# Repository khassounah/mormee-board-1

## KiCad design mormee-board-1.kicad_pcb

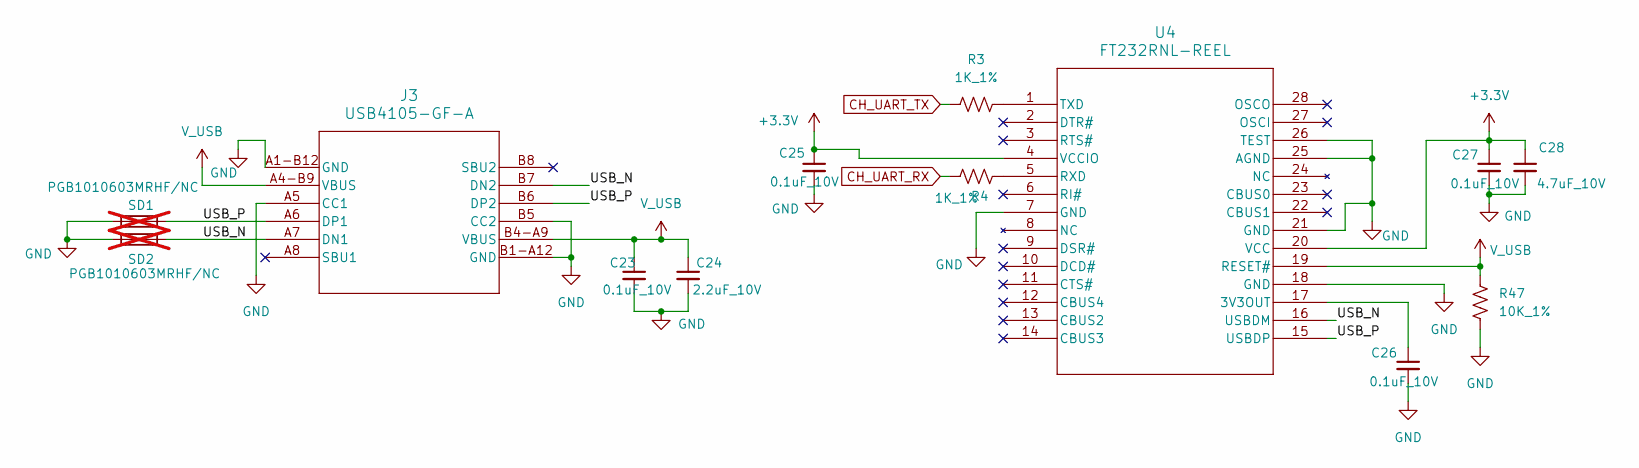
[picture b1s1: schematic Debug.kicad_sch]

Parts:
C23, C25, C26, C27: 0.1uF_10V; C_0603_1608Metric
C24: 2.2uF_10V; C_0603_1608Metric
C28: 4.7uF_10V; C_0603_1608Metric
J3: USB4105-GF-A; USB4105_GCT
R3, R4: 1K_1%; R_0603_1608Metric
R47: 10K_1%; R_0603_1608Metric
SD1, SD2: PGB1010603MRHF/NC; Fuse_0603_1608Metric; not fitted
U4: FT232RNL-REEL; SSOP-28_FTD

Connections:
+3.3V: C25.1, C27.1, C28.1, U4.4 (VCCIO), U4.20 (VCC); also elsewhere on the board
/Debug Interface/USB_N: J3.A7 (DN1), J3.B7 (DN2), SD2.2, U4.16 (USBDM)
/Debug Interface/USB_P: J3.A6 (DP1), J3.B6 (DP2), SD1.2, U4.15 (USBDP)
CH_UART_RX: R4.1; also elsewhere on the board
CH_UART_TX: R3.2; also elsewhere on the board
GND: C23.2, C24.2, C25.2, C26.2, C27.2, C28.2, J3.A1-B12 (GND), J3.A5 (CC1), J3.B1-A12 (GND), J3.B5 (CC2), R47.2, SD1.1, SD2.1, U4.7 (GND), U4.18 (GND), U4.21 (GND), U4.25 (AGND), U4.26 (TEST); also elsewhere on the board
unnamed: C26.1, U4.17 (3V3OUT)
unnamed: R4.2, U4.5 (RXD)
unnamed: R3.1, U4.1 (TXD)
V_USB: C23.1, C24.1, J3.A4-B9 (VBUS), J3.B4-A9 (VBUS), R47.1, U4.19 (RESET#); also elsewhere on the board

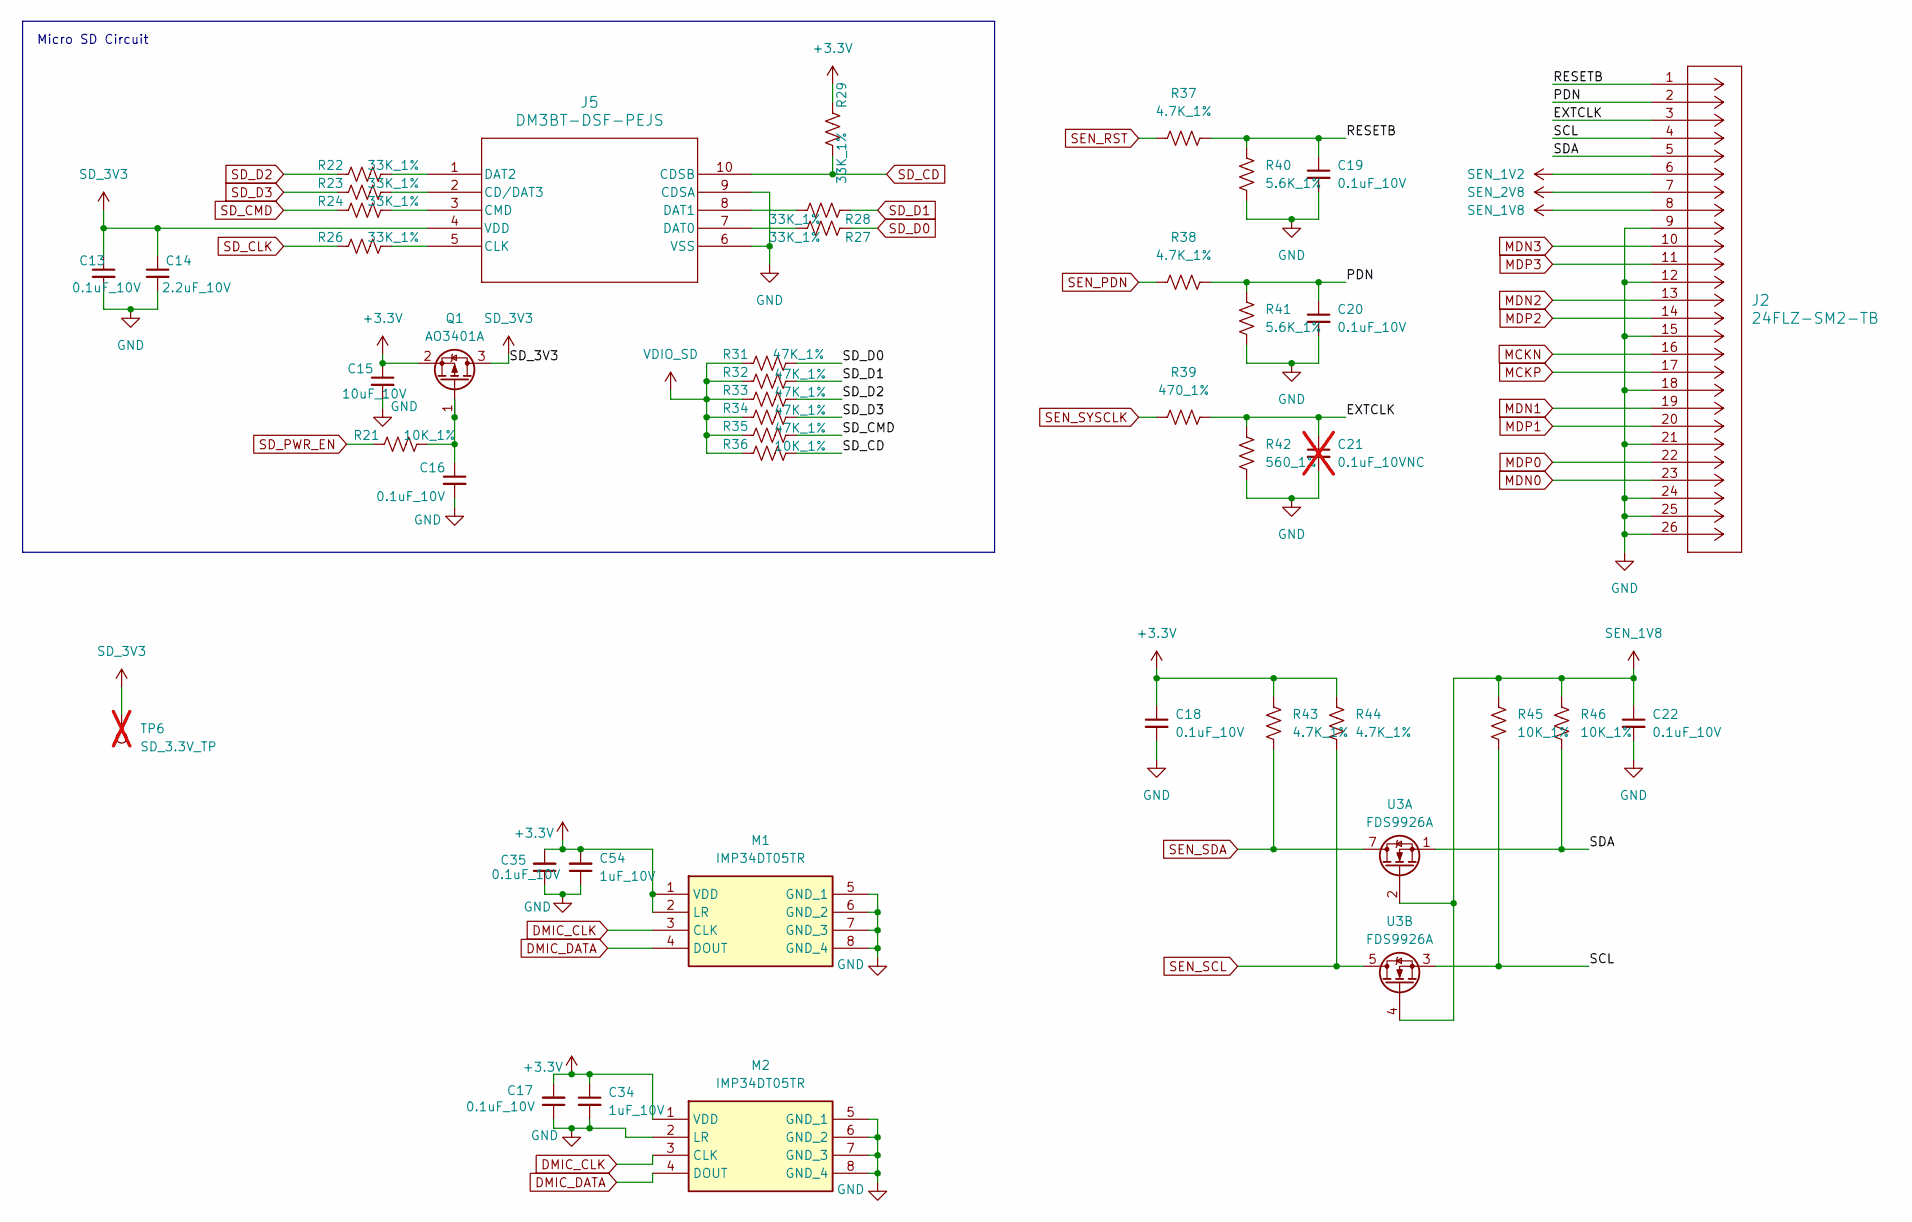
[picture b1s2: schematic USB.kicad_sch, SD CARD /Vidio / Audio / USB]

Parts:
C13, C16, C17, C18, C19, C20, C22, C35: 0.1uF_10V; C_0603_1608Metric
C14: 2.2uF_10V; C_0603_1608Metric
C15: 10uF_10V; C_0603_1608Metric
C21: 0.1uF_10VNC; C_0603_1608Metric; not fitted
C34, C54: 1uF_10V; C_0603_1608Metric
J2: 24FLZ-SM2-TB; CON24_1X24_DB_JST
J5: DM3BT-DSF-PEJS; DM3BT-DSF-PEJS_HIR
M1, M2: IMP34DT05TR; Manufacturer_Part_Number IMP34DT05TR; Mouser Part Number 511-IMP34DT05TR
Q1: AO3401A; SOT-23
R21, R36, R45, R46: 10K_1%; R_0603_1608Metric
R22, R23, R24, R26, R27, R28, R29: 33K_1%; R_0603_1608Metric
R31, R32, R33, R34, R35: 47K_1%; R_0603_1608Metric
R37, R38, R43, R44: 4.7K_1%; R_0603_1608Metric
R39: 470_1%; R_0603_1608Metric
R40, R41: 5.6K_1%; R_0603_1608Metric
R42: 560_1%; R_0603_1608Metric
TP6: SD_3.3V_TP; TestPoint_Pad_D1.5mm; not fitted
U3: FDS9926A; SOIC-8_3.9x4.9mm_P1.27mm

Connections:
+3.3V: C15.1, C17.2, C18.1, C34.1, C35.2, C54.2, M1.1 (VDD), M1.2 (LR), M2.1 (VDD), Q1.2 (S), R29.1, R43.1, R44.1; also elsewhere on the board
/SD CARD /Vidio / Audio / USB/EXTCLK: C21.1, J2.3, R39.1, R42.1
/SD CARD /Vidio / Audio / USB/PDN: C20.1, J2.2, R38.1, R41.1
/SD CARD /Vidio / Audio / USB/RESETB: C19.1, J2.1, R37.1, R40.1
/SD CARD /Vidio / Audio / USB/SCL: J2.4, R45.2, U3.3 (S2)
/SD CARD /Vidio / Audio / USB/SDA: J2.5, R46.2, U3.1 (S1)
DMIC_CLK: M1.3 (CLK), M2.3 (CLK); also elsewhere on the board
DMIC_DATA: M1.4 (DOUT), M2.4 (DOUT); also elsewhere on the board
GND: C13.2, C14.2, C15.2, C16.2, C17.1, C18.2, C19.2, C20.2, C21.2, C22.2, C34.2, C35.1, C54.1, J2.9, J2.12, J2.15, J2.18, J2.21, J2.24, J2.25, J2.26, J5.6 (VSS), J5.9 (CDSA), M1.5 (GND_1), M1.6 (GND_2), M1.7 (GND_3), M1.8 (GND_4), M2.2 (LR), M2.5 (GND_1), M2.6 (GND_2), M2.7 (GND_3), M2.8 (GND_4), R40.2, R41.2, R42.2; also elsewhere on the board
MCKN: J2.16; also elsewhere on the board
MCKP: J2.17; also elsewhere on the board
MDN0: J2.23; also elsewhere on the board
MDN1: J2.19; also elsewhere on the board
MDN2: J2.13; also elsewhere on the board
MDN3: J2.10; also elsewhere on the board
MDP0: J2.22; also elsewhere on the board
MDP1: J2.20; also elsewhere on the board
MDP2: J2.14; also elsewhere on the board
MDP3: J2.11; also elsewhere on the board
unnamed: J5.2 (CD/DAT3), R23.2
unnamed: J5.5 (CLK), R26.2
unnamed: J5.3 (CMD), R24.2
unnamed: J5.7 (DAT0), R27.2
unnamed: J5.8 (DAT1), R28.2
unnamed: J5.1 (DAT2), R22.2
unnamed: C16.1, Q1.1 (G), R21.2
SD_3V3: C13.1, C14.1, J5.4 (VDD), Q1.3 (D), TP6.1
SD_CD: J5.10 (CDSB), R29.2, R36.2; also elsewhere on the board
SD_CLK: R26.1; also elsewhere on the board
SD_CMD: R24.1, R35.2; also elsewhere on the board
SD_D0: R27.1, R31.2; also elsewhere on the board
SD_D1: R28.1, R32.2; also elsewhere on the board
SD_D2: R22.1, R33.2; also elsewhere on the board
SD_D3: R23.1, R34.2; also elsewhere on the board
SD_PWR_EN: R21.1; also elsewhere on the board
SEN_1V2: J2.6; also elsewhere on the board
SEN_1V8: C22.1, J2.8, R45.1, R46.1, U3.2 (G1), U3.4 (G2); also elsewhere on the board
SEN_2V8: J2.7; also elsewhere on the board
SEN_PDN: R38.2; also elsewhere on the board
SEN_RST: R37.2; also elsewhere on the board
SEN_SCL: R44.2, U3.5 (D2), U3.6 (D2); also elsewhere on the board
SEN_SDA: R43.2, U3.7 (D1), U3.8 (D1); also elsewhere on the board
SEN_SYSCLK: R39.2; also elsewhere on the board
VDIO_SD: R31.1, R32.1, R33.1, R34.1, R35.1, R36.1; also elsewhere on the board

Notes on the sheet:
Micro SD Circuit

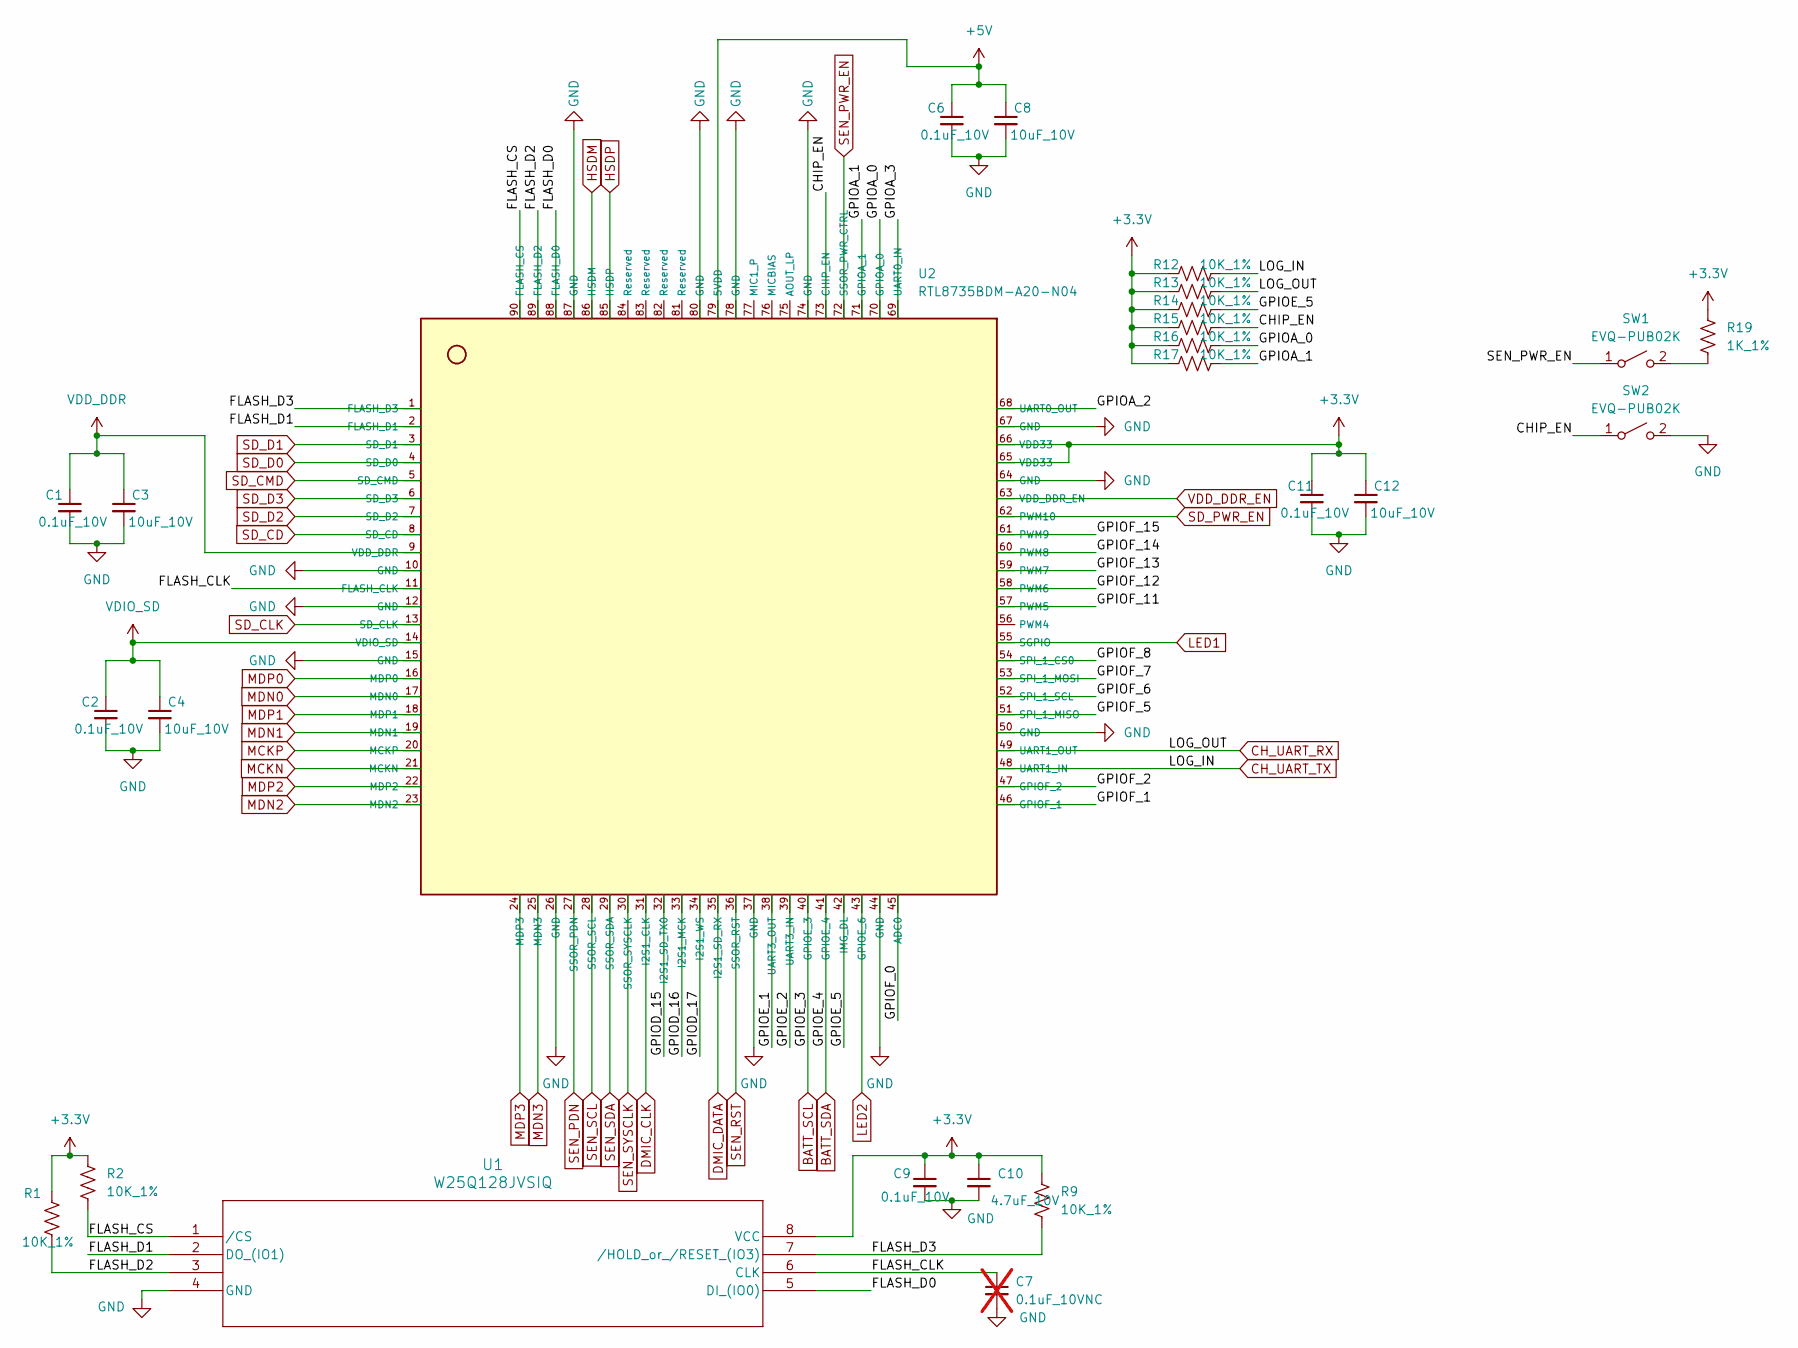
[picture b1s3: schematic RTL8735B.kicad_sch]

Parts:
C1, C2, C6, C9, C11: 0.1uF_10V; C_0603_1608Metric
C3, C4, C8, C12: 10uF_10V; C_0603_1608Metric
C7: 0.1uF_10VNC; C_0603_1608Metric; not fitted
C10: 4.7uF_10V; C_0603_1608Metric
R1, R2, R9, R12, R13, R14, R15, R16, R17: 10K_1%; R_0603_1608Metric
R19: 1K_1%; R_0603_1608Metric
SW1, SW2: EVQ-PUB02K; Panasonic_EVQPUK_EVQPUB
U1: W25Q128JVSIQ; SOIC_128JVSIQ_WIN
U2: RTL8735BDM-A20-N04

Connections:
+3.3V: C9.1, C10.1, C11.1, C12.1, R1.1, R2.1, R9.1, R12.1, R13.1, R14.1, R15.1, R16.1, R17.1, R19.1, U1.8 (VCC), U2.65 (VDD33), U2.66 (VDD33); also elsewhere on the board
+5V: C6.1, C8.1, U2.79 (5VDD); also elsewhere on the board
/RTL9835B/CHIP_EN: R15.2, SW2.1 (A), U2.73 (CHIP_EN)
/RTL9835B/FLASH_CLK: C7.1, U1.6 (CLK), U2.11 (FLASH_CLK)
/RTL9835B/FLASH_CS: R2.2, U1.1 (/CS), U2.90 (FLASH_CS)
/RTL9835B/FLASH_D0: U1.5 (DI_(IO0)), U2.88 (FLASH_D0)
/RTL9835B/FLASH_D1: U1.2 (DO_(IO1)), U2.2 (FLASH_D1)
/RTL9835B/FLASH_D2: R1.2, U1.3, U2.89 (FLASH_D2)
/RTL9835B/FLASH_D3: R9.2, U1.7 (/HOLD_or_/RESET_(IO3)), U2.1 (FLASH_D3)
/RTL9835B/GPIOA_0: R16.2, U2.70 (GPIOA_0)
/RTL9835B/GPIOA_1: R17.2, U2.71 (GPIOA_1)
/RTL9835B/GPIOA_2: U2.68 (UART0_OUT)
/RTL9835B/GPIOA_3: U2.69 (UART0_IN)
/RTL9835B/GPIOD_15: U2.32 (I2S1_SD_TX0)
/RTL9835B/GPIOD_16: U2.33 (I2S1_MCK)
/RTL9835B/GPIOD_17: U2.34 (I2S1_WS)
/RTL9835B/GPIOE_1: U2.38 (UART3_OUT)
/RTL9835B/GPIOE_2: U2.39 (UART3_IN)
/RTL9835B/GPIOE_5: R14.2, U2.42 (IMG_DL)
/RTL9835B/GPIOF_0: U2.45 (ADC0)
/RTL9835B/GPIOF_1: U2.46 (GPIOF_1)
/RTL9835B/GPIOF_2: U2.47 (GPIOF_2)
/RTL9835B/GPIOF_5: U2.51 (SPI_1_MISO)
/RTL9835B/GPIOF_6: U2.52 (SPI_1_SCL)
/RTL9835B/GPIOF_7: U2.53 (SPI_1_MOSI)
/RTL9835B/GPIOF_8: U2.54 (SPI_1_CS0)
/RTL9835B/GPIOF_11: U2.57 (PWM5)
/RTL9835B/GPIOF_12: U2.58 (PWM6)
/RTL9835B/GPIOF_13: U2.59 (PWM7)
/RTL9835B/GPIOF_14: U2.60 (PWM8)
/RTL9835B/GPIOF_15: U2.61 (PWM9)
BATT_SCL: U2.40 (GPIOE_3); also elsewhere on the board
BATT_SDA: U2.41 (GPIOE_4); also elsewhere on the board
CH_UART_RX: R13.2, U2.49 (UART1_OUT); also elsewhere on the board
CH_UART_TX: R12.2, U2.48 (UART1_IN); also elsewhere on the board
DMIC_CLK: U2.31 (I2S1_CLK); also elsewhere on the board
DMIC_DATA: U2.35 (I2S1_SD_RX); also elsewhere on the board
GND: C1.2, C2.2, C3.2, C4.2, C6.2, C7.2, C8.2, C9.2, C10.2, C11.2, C12.2, SW2.2 (B), U1.4 (GND), U2.10 (GND), U2.12 (GND), U2.15 (GND), U2.26 (GND), U2.37 (GND), U2.44 (GND), U2.50 (GND), U2.64 (GND), U2.67 (GND), U2.74 (GND), U2.78 (GND), U2.80 (GND), U2.87 (GND); also elsewhere on the board
HSDM: U2.86 (HSDM)
HSDP: U2.85 (HSDP)
LED1: U2.55 (SGPIO)
LED2: U2.43 (GPIOE_6)
MCKN: U2.21 (MCKN); also elsewhere on the board
MCKP: U2.20 (MCKP); also elsewhere on the board
MDN0: U2.17 (MDN0); also elsewhere on the board
MDN1: U2.19 (MDN1); also elsewhere on the board
MDN2: U2.23 (MDN2); also elsewhere on the board
MDN3: U2.25 (MDN3); also elsewhere on the board
MDP0: U2.16 (MDP0); also elsewhere on the board
MDP1: U2.18 (MDP1); also elsewhere on the board
MDP2: U2.22 (MDP2); also elsewhere on the board
MDP3: U2.24 (MDP3); also elsewhere on the board
unnamed: R19.2, SW1.2 (B)
SD_CD: U2.8 (SD_CD); also elsewhere on the board
SD_CLK: U2.13 (SD_CLK); also elsewhere on the board
SD_CMD: U2.5 (SD_CMD); also elsewhere on the board
SD_D0: U2.4 (SD_D0); also elsewhere on the board
SD_D1: U2.3 (SD_D1); also elsewhere on the board
SD_D2: U2.7 (SD_D2); also elsewhere on the board
SD_D3: U2.6 (SD_D3); also elsewhere on the board
SD_PWR_EN: U2.62 (PWM10); also elsewhere on the board
SEN_PDN: U2.27 (SSOR_PDN); also elsewhere on the board
SEN_PWR_EN: SW1.1 (A), U2.72 (SSOR_PWR_CTRL); also elsewhere on the board
SEN_RST: U2.36 (SSOR_RST); also elsewhere on the board
SEN_SCL: U2.28 (SSOR_SCL); also elsewhere on the board
SEN_SDA: U2.29 (SSOR_SDA); also elsewhere on the board
SEN_SYSCLK: U2.30 (SSOR_SYSCLK); also elsewhere on the board
VDD_DDR: C1.1, C3.1, U2.9 (VDD_DDR); also elsewhere on the board
VDD_DDR_EN: U2.63 (VDD_DDR_EN); also elsewhere on the board
VDIO_SD: C2.1, C4.1, U2.14 (VDIO_SD); also elsewhere on the board

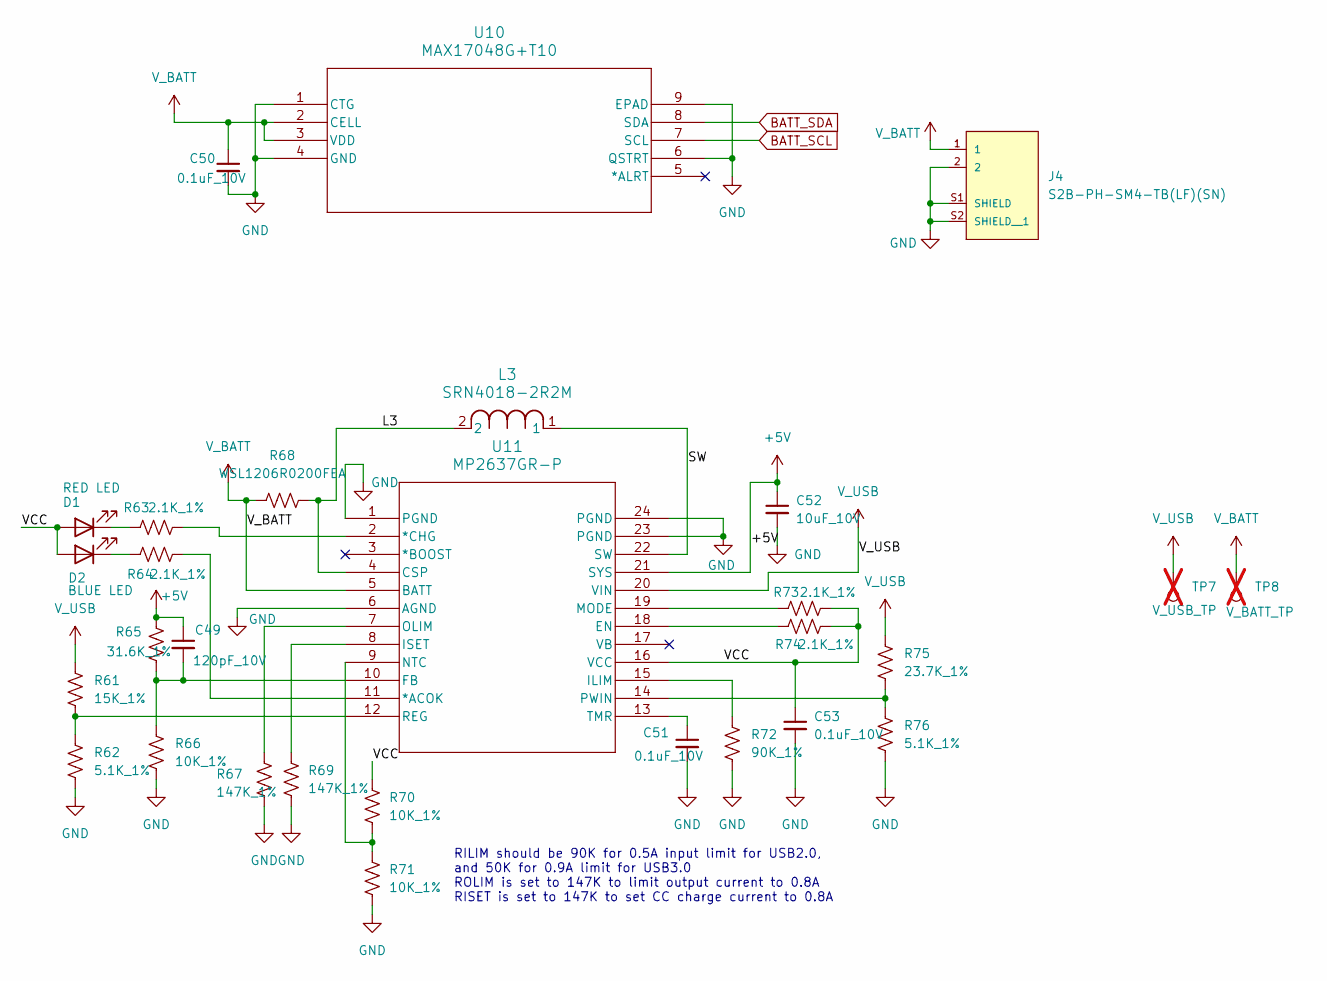
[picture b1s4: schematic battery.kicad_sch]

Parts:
C49: 120pF_10V; C_0603_1608Metric
C50, C51, C53: 0.1uF_10V; C_0603_1608Metric
C52: 10uF_10V; C_0603_1608Metric
D1: RED LED; LED_0603_1608Metric
D2: BLUE LED; LED_0603_1608Metric
J4: S2B-PH-SM4-TB(LF)(SN); JST_S2B-PH-SM4-TB_LF__SN_
L3: SRN4018-2R2M; IND_BOURNS_SRN4018
R61: 15K_1%; R_0603_1608Metric
R62, R76: 5.1K_1%; R_0603_1608Metric
R63, R64, R73, R74: 2.1K_1%; R_0603_1608Metric
R65: 31.6K_1%; R_0603_1608Metric
R66, R70, R71: 10K_1%; R_0603_1608Metric
R67, R69: 147K_1%; R_0603_1608Metric
R68: WSL1206R0200FEA; R_1206_3216Metric
R72: 90K_1%; R_0603_1608Metric
R75: 23.7K_1%; R_0603_1608Metric
TP7: V_USB_TP; TestPoint_Pad_D1.5mm; not fitted
TP8: V_BATT_TP; TestPoint_Pad_D1.5mm; not fitted
U10: MAX17048G+T10; 21-0168E_T822-3_MXM
U11: MP2637GR-P; QFN-24_MP2637_MNP

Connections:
+5V: C49.1, C52.1, R65.1, U11.21 (SYS); also elsewhere on the board
/Battery/L3: L3.2, R68.2, U11.4 (CSP)
/Battery/SW: L3.1, U11.22 (SW)
/Battery/VCC: C53.1, D1.2 (A), D2.2 (A), R70.1, R73.1, R74.2, U11.16 (VCC)
BATT_SCL: U10.7 (SCL); also elsewhere on the board
BATT_SDA: U10.8 (SDA); also elsewhere on the board
GND: C50.2, C51.2, C52.2, C53.2, J4.2, J4.S1 (SHIELD), J4.S2 (SHIELD__1), R62.2, R66.2, R67.2, R69.2, R71.2, R72.2, R76.2, U10.1 (CTG), U10.4 (GND), U10.6 (QSTRT), U10.9 (EPAD), U11.1 (PGND), U11.6 (AGND), U11.23 (PGND), U11.24 (PGND); also elsewhere on the board
unnamed: D1.1 (K), R63.1
unnamed: D2.1 (K), R64.1
unnamed: R64.2, U11.11 (*ACOK)
unnamed: R63.2, U11.2 (*CHG)
unnamed: R74.1, U11.18 (EN)
unnamed: C49.2, R65.2, R66.1, U11.10 (FB)
unnamed: R72.1, U11.15 (ILIM)
unnamed: R69.1, U11.8 (ISET)
unnamed: R73.2, U11.19 (MODE)
unnamed: R70.2, R71.1, U11.9 (NTC)
unnamed: R67.1, U11.7 (OLIM)
unnamed: R75.2, R76.1, U11.14 (PWIN)
unnamed: R61.2, R62.1, U11.12 (REG)
unnamed: C51.1, U11.13 (TMR)
V_BATT: C50.1, J4.1, R68.1, TP8.1, U10.2 (CELL), U10.3 (VDD), U11.5 (BATT)
V_USB: R61.1, R75.1, TP7.1, U11.20 (VIN); also elsewhere on the board

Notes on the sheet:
RILIM should be 90K for 0.5A input limit for USB2.0, and 50K for 0.9A limit for USB3.0 ROLIM is set to 147K to limit output current to 0.8A RISET is set to 147K to set CC charge current to 0.8A

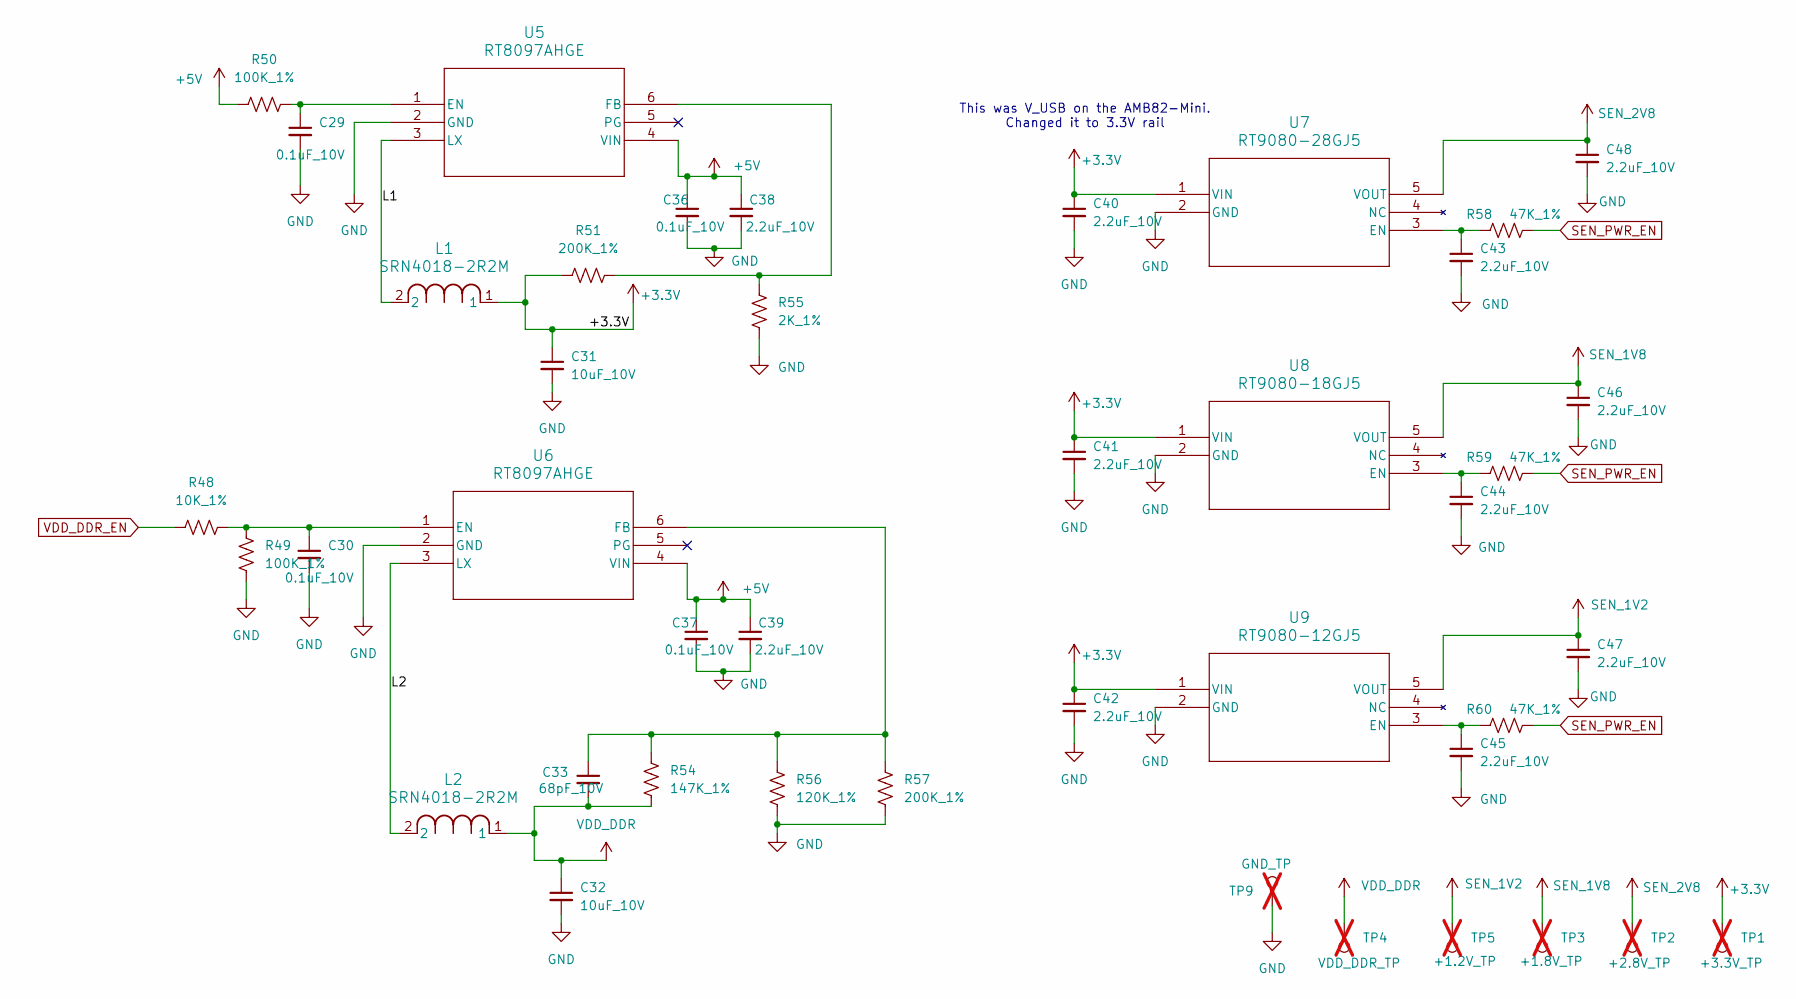
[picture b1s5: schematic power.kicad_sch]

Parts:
C29, C30, C36, C37: 0.1uF_10V; C_0603_1608Metric
C31, C32: 10uF_10V; C_0603_1608Metric
C33: 68pF_10V; C_0603_1608Metric
C38, C39, C40, C41, C42, C43, C44, C45, C46, C47, C48: 2.2uF_10V; C_0603_1608Metric
L1, L2: SRN4018-2R2M; IND_BOURNS_SRN4018
R48: 10K_1%; R_0603_1608Metric
R49, R50: 100K_1%; R_0603_1608Metric
R51, R57: 200K_1%; R_0603_1608Metric
R54: 147K_1%; R_0603_1608Metric
R55: 2K_1%; R_0603_1608Metric
R56: 120K_1%; R_0603_1608Metric
R58, R59, R60: 47K_1%; R_0603_1608Metric
TP1: +3.3V_TP; TestPoint_Pad_D1.5mm; not fitted
TP2: +2.8V_TP; TestPoint_Pad_D1.5mm; not fitted
TP3: +1.8V_TP; TestPoint_Pad_D1.5mm; not fitted
TP4: VDD_DDR_TP; TestPoint_Pad_D1.5mm; not fitted
TP5: +1.2V_TP; TestPoint_Pad_D1.5mm; not fitted
TP9: GND_TP; TestPoint_Pad_D1.5mm; not fitted
U5, U6: RT8097AHGE; SOT-23-6_Handsoldering
U7: RT9080-28GJ5; TSOT-23-5_RIT
U8: RT9080-18GJ5; TSOT-23-5_RIT
U9: RT9080-12GJ5; TSOT-23-5_RIT

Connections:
+3.3V: C31.1, C40.1, C41.1, C42.1, L1.1, R51.1, TP1.1, U7.1 (VIN), U8.1 (VIN), U9.1 (VIN); also elsewhere on the board
+5V: C36.1, C37.1, C38.1, C39.1, R50.1, U5.4 (VIN), U6.4 (VIN); also elsewhere on the board
/Power/L1: L1.2, U5.3 (LX)
/Power/L2: L2.2, U6.3 (LX)
GND: C29.2, C30.2, C31.2, C32.2, C36.2, C37.2, C38.2, C39.2, C40.2, C41.2, C42.2, C43.2, C44.2, C45.2, C46.2, C47.2, C48.2, R49.1, R55.2, R56.2, R57.2, TP9.1, U5.2 (GND), U6.2 (GND), U7.2 (GND), U8.2 (GND), U9.2 (GND); also elsewhere on the board
unnamed: C29.1, R50.2, U5.1 (EN)
unnamed: R51.2, R55.1, U5.6 (FB)
unnamed: C30.1, R48.2, R49.2, U6.1 (EN)
unnamed: C33.1, R54.2, R56.1, R57.1, U6.6 (FB)
unnamed: C43.1, R58.1, U7.3 (EN)
unnamed: C44.1, R59.1, U8.3 (EN)
unnamed: C45.1, R60.1, U9.3 (EN)
SEN_1V2: C47.1, TP5.1, U9.5 (VOUT); also elsewhere on the board
SEN_1V8: C46.1, TP3.1, U8.5 (VOUT); also elsewhere on the board
SEN_2V8: C48.1, TP2.1, U7.5 (VOUT); also elsewhere on the board
SEN_PWR_EN: R58.2, R59.2, R60.2; also elsewhere on the board
VDD_DDR: C32.1, C33.2, L2.1, R54.1, TP4.1; also elsewhere on the board
VDD_DDR_EN: R48.1; also elsewhere on the board

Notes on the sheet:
This was V_USB on the AMB82-Mini. Changed it to 3.3V rail

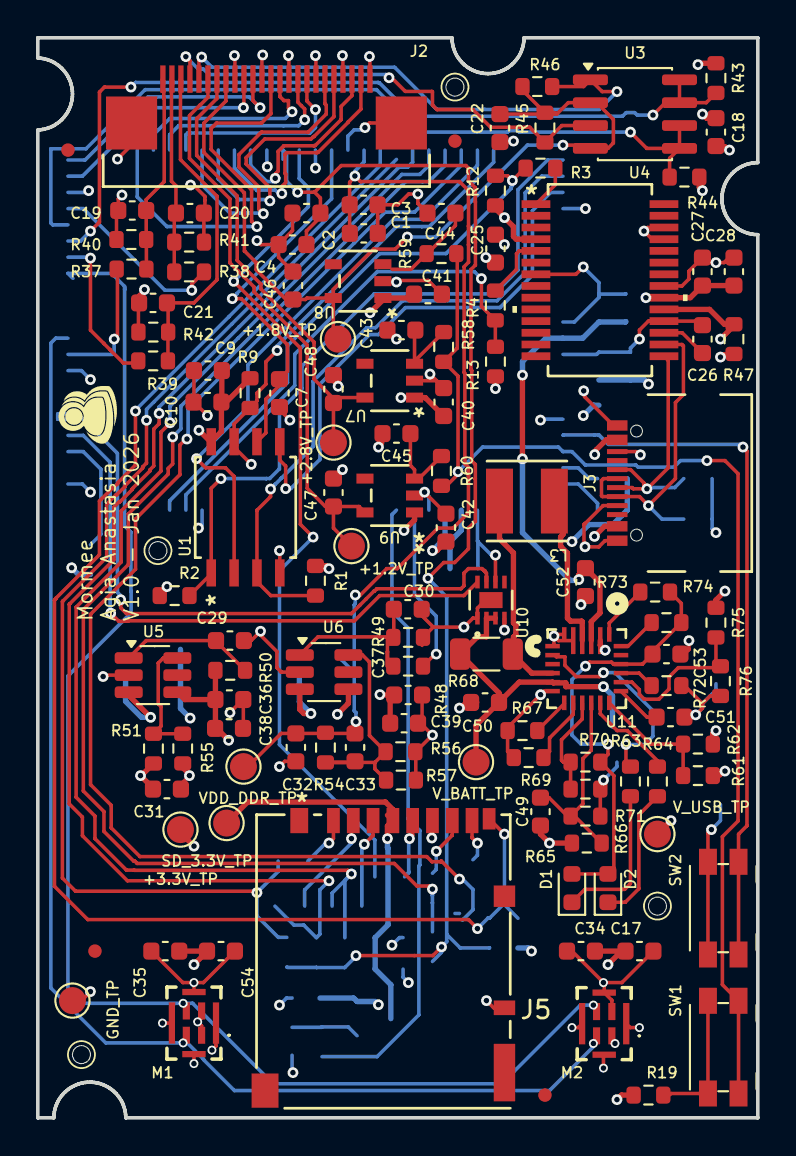
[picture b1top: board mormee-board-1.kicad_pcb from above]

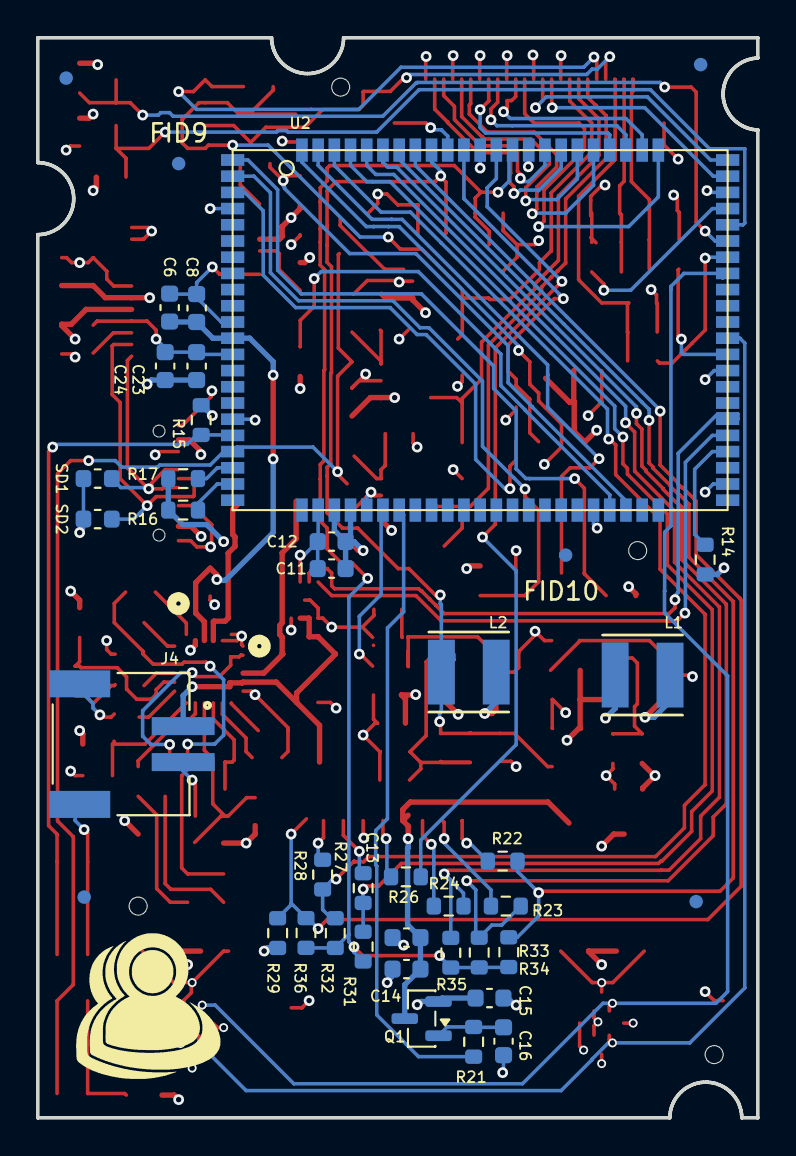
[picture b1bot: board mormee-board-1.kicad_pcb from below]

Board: 4 copper layers, 40.0 x 60.0 mm, 167 parts (41 on the bottom side), 96 nets.

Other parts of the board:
FID1, FID2, FID3, FID4, FID5, FID6, FID7, FID8, FID9, FID10: Fiducial; Fiducial_0.75mm_Mask1.5mm
H1, H2, H3, H4: MountingHole; MountingHole_1mm

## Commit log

2026-01-15 All key features are in the schematic.
2026-01-21 All footprints configured correctly. Next step is layout
2026-01-24 In the middle of layout. WIP
2026-01-30 Breakthrough in PCB layout. WIP
2026-01-31 Most signals routed. Just need power plane clean up and final checks. Almost there, but WIP
2026-01-31 All nets seem to be routed. Checkingo
2026-02-01 Board is fully routed
2026-02-01 Added text and logo
2026-02-01 I think I'm done. Fingers crossed.
2026-02-02 Added mounting holes and alignment notches
2026-02-02 Ready. I think. At last. Probably.
2026-02-02 Final V1.0 commit
2026-02-02 Now v1.0 is complete
2026-02-02 Added 1k resistors in series with the FTDI Tx & Rx lines. This was recommended by Gemini to protect when the VCC is unpowered to the FTDI chip, and we're running from battery.
2026-02-02 Updated gerbers for official v1.0
2026-02-03 Replaced all passive footprints from 0603 metric to 0603 imperial. Big oversight. All done. Next is DRC
2026-02-03 All footprints are humanly visible (using imperial 0603), no meaningful DRC issues, and looking good.
2026-02-03 All fiducials and mounting holes placed. Except one hole, which I'll try to place. WIP
2026-02-03 This should be it. Gerber files with drill files generated.
2026-02-03 Updated LED footprint to 0603, which was easier to find
2026-02-03 Fixed R55 value
2026-02-04 Updated USB connector pads to be manufacturable
2026-02-04 Final final gerbers
2026-02-04 Renamed markers file
